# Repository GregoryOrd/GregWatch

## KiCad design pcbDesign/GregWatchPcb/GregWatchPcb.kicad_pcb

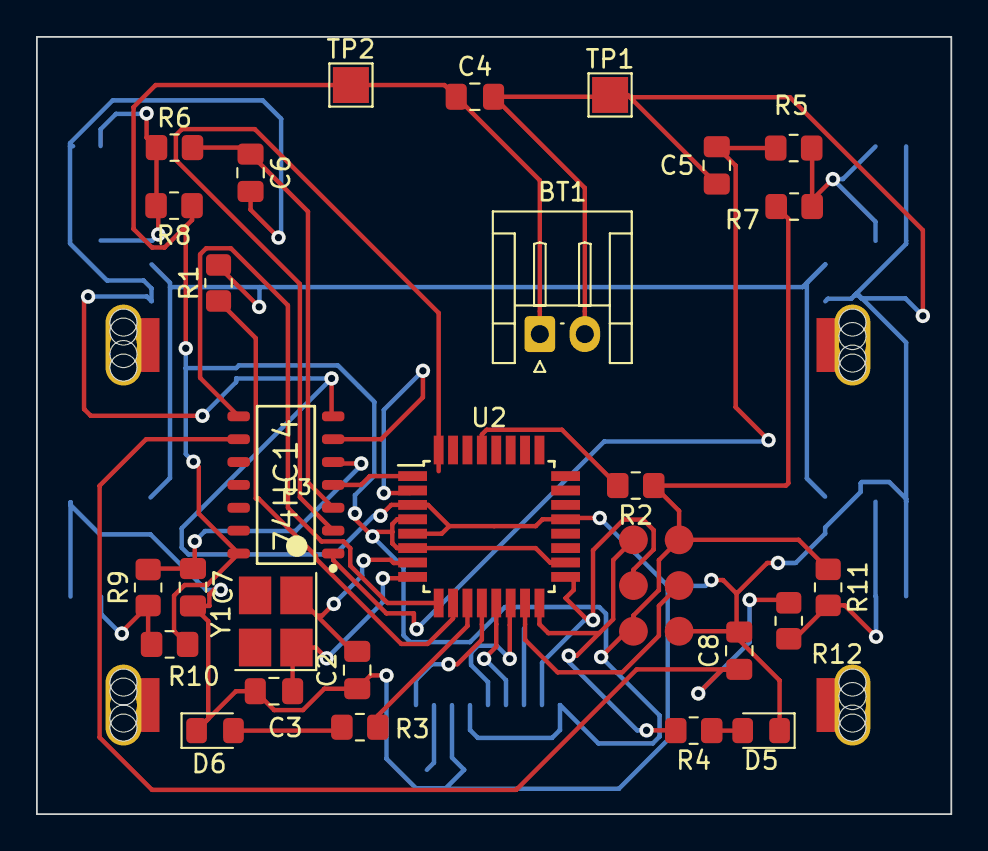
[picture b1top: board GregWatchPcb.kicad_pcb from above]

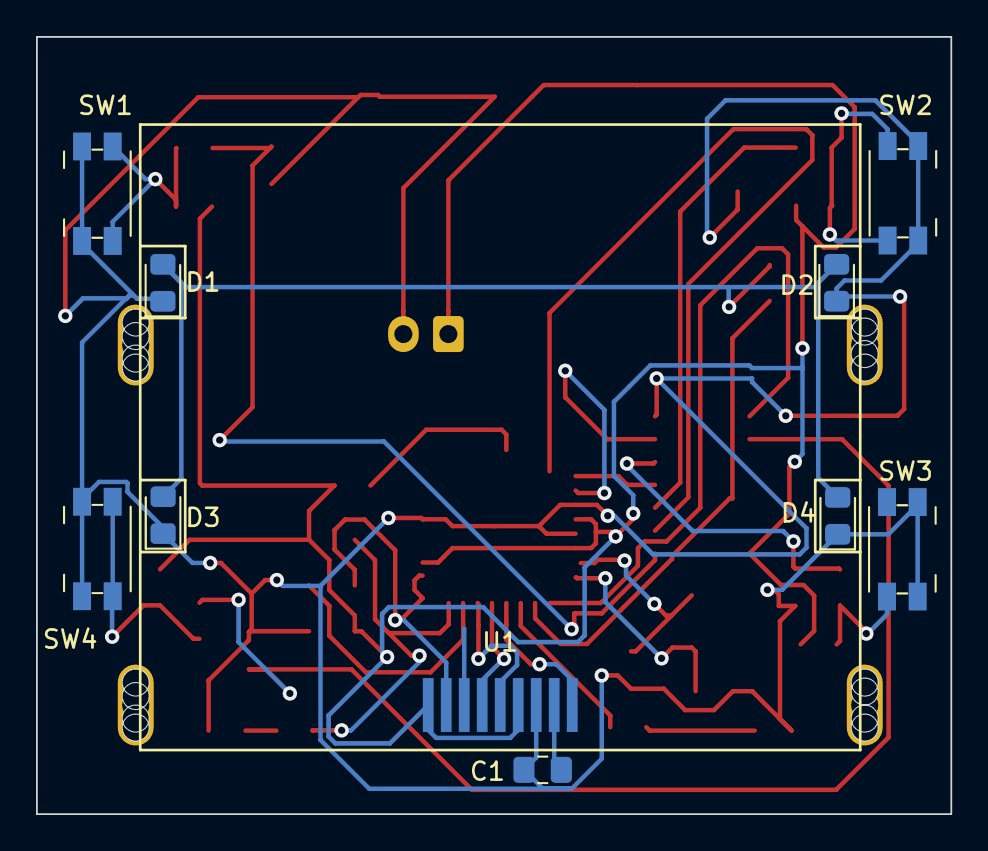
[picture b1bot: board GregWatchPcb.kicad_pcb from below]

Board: 2 copper layers, 50.8 x 43.2 mm, 38 parts (10 on the bottom side), 29 nets.

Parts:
BT1: Battery_Cell; JST_EH_S2B-EH_1x02_P2.50mm_Horizontal
C1, C5, C6, C7, C8: 0.1u; C_0805_2012Metric_Pad1.18x1.45mm_HandSolder
C2, C3: 22p; C_0805_2012Metric_Pad1.18x1.45mm_HandSolder
C4: 10u; C_0805_2012Metric_Pad1.18x1.45mm_HandSolder
D1, D2, D3, D4, D5, D6: LED; LED_0805_2012Metric_Pad1.15x1.40mm_HandSolder
J1: AVR-ISP-6
R1, R3, R4: 100; R_0805_2012Metric_Pad1.20x1.40mm_HandSolder
R2, R5, R6, R7, R8, R9, R10, R11, R12: 10k; R_0805_2012Metric_Pad1.20x1.40mm_HandSolder
SW1, SW2, SW3, SW4: SW_Push; Panasonic_EVQPUJ_EVQPUA
TP1, TP2: TestPoint; TestPoint_Pad_2.0x2.0mm
U1: Nokia_5110_LCD; Nokia_5110-3310_LCD-F.Paste-B.Paste
U2: ATmega328P-AU; TQFP-32_7x7mm_P0.8mm
U3: 74HC14; Texas_Instruments-CD74HC14-Level_C
Y1: 16M; Crystal_SMD_3225-4Pin_3.2x2.5mm_HandSoldering

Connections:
unnamed: BT1.1, C4.1, J1.2, J1.5, R2.1, R7.1, R8.1, R10.1, R11.1, TP2.1, U1.4, U1.9, U2.4, U2.6, U2.18, U3.14
unnamed: BT1.2, C1.1, C2.1, C3.1, C4.2, C5.2, C6.2, C7.2, C8.2, D1.1, D2.1, D3.1, D4.1, D5.1, D6.1, J1.6, SW1.1, SW2.1, SW3.1, SW4.1, TP1.1, U1.3, U2.3, U2.5, U2.21, U3.7
unnamed: C1.2, U1.2
unnamed: C2.2, U2.7, Y1.2
unnamed: C3.2, U2.8, Y1.1
unnamed: C5.1, R5.2, U3.1
unnamed: C6.1, R6.2, U3.3
unnamed: C7.1, R9.2, U3.5
unnamed: C8.1, R12.2, U3.9
unnamed: D1.2, D2.2, D3.2, D4.2, R1.2
unnamed: D5.2, R4.1
unnamed: D6.2, R3.1
unnamed: J1.1, R4.2, U2.16
unnamed: J1.3, U1.8, U2.17
unnamed: J1.4, U1.7, U2.15
unnamed: R1.1, U2.10
unnamed: R2.2, U2.29
unnamed: R3.2, U2.11
unnamed: R5.1, R7.2, SW1.2
unnamed: R6.1, R8.2, SW2.2
unnamed: R9.1, R10.2, SW3.2
unnamed: R11.2, R12.1, SW4.2
unnamed: U1.1, U2.12
unnamed: U1.5, U2.14
unnamed: U1.6, U2.13
unnamed: U2.1, U3.4
unnamed: U2.2, U3.6
unnamed: U2.9, U3.8
unnamed: U2.32, U3.2

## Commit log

2021-04-19 First code commit with copied code for an example to drive the LCD screen
2021-04-19 Actual first code commit.
2021-04-19 Correcting GregBuild config file and the load.sh and copy.sh scripts
2021-04-19 Now showing a timer at 00:00 and switching to 00:01 after one second
2021-04-20 Major cleanup. Now have the display bit patterns for numbers 0 through 2 as well as a colon. Can run through a clock like pattern with minutes and hours going up to 22.
2021-04-27 Added -fno-common linker flag
2021-04-27 Adding the bit pattern for number 3
2021-04-27 Adding reset display functions and using loops to run through minutes and hours.
2021-04-27 Add bit pattern for number 4 and made number 3 a touch wider.
2021-04-27 Shortened number of lines in run through functions.
2021-04-28 Add bit patterns for six and seven
2021-04-28 Added number 7
2021-04-28 Improved bit pattern for 7 to have a diagonal leg.
2021-04-28 Bit pattern for number 8
2021-04-28 Added bit pattern for 9
2021-04-28 Cleanup the runThroughMinutes and runThroughHours functions.
2021-04-29 Restructured the repo. Prep work for linking with a hardware sim library. Need to wait on some more functionality to be built into GregBuild to support this.
2021-04-29 First failing test after GregBuild update. hardwareSim.so and timeSim.so now found under the repo/s lib directory.
2021-04-29 Makefile for creating the hardware simulator libraries.
2021-04-29 Rename and passing the first test.
2021-04-29 Created TODOs.txt
2021-04-30 Test cases for all functions in spi.h. Some commented out while waiting for updates to GregTest
2021-04-30 Back out of the SPI directory
2021-05-01 Move around spi.h includes
2021-05-01 Added testNokia5110.c
2021-05-01 Major reorganization of the repo. Trying to think about the structure as features and subfeatures.
2021-05-01 Create timeDefs.h. Rename functions/variables to match that right now, our display is minutes:seconds not hours:minutes.
2021-05-01 Added TestTimeDefs.c
2021-05-02 Adding compiler option to allow for G_EXPECT_CALLs
2021-05-02 Using expect calls and bool comparisions now that they are supported by GregTest.
2021-05-04 Wrote test cases for testStopWatch.c
2021-05-04 Added test cases in testLetters16x12.c
2021-05-07 Switching to a timer interrupt instead of _delay_ms for the stop watch.
2021-05-07 Adding a stopWatchDone flag for hitting 60 minutes,
2021-05-08 Add #define IDR to the hardwareSim to get rid of error when compiling for tests.
2021-05-08 Move time related files to timer directory
2021-05-08 Pull presentation folder out a layer
2021-05-08 Removed the screenApi layer folder
2021-05-09 First version of the stop and start button.
2021-06-04 Created fuses.txt to record what configuration is being used for the fuse bits on the AtMega328p microcontroller.
2021-06-06 Using INT0 for the pause button.
2021-06-10 Starting to put together a schematic using KiCad
2021-06-11 Move SPI lines for screen to the right
2021-06-11 Using nokia 5110 schematic symbol
2021-06-11 Add backlight LEDs and button circuits
2021-06-11 Added resistance and capacitance values to all resistors and capacitors
2021-06-11 Annotated schematic and corrected some RC values
2021-06-11 Added note about part names/numbers for purchasing components
2021-06-13 Added footprints to the schematic components
2021-06-13 Add number of each component nessecary to components list text file
2021-06-13 Exported schematic as netlist and imported it into Pcbnew
2021-06-15 Screen and backlight LED components arranged on the back of the PCB
2021-06-15 Move LEDs and flip capacitor and resistor to make sure things fit under the clip on screen
2021-06-15 Moved switched and ISP pad in place. Only partial connections so far.
2021-06-16 Switch interrupt to rising edge for on-press behaviour instead of on-release behaviour
2021-06-16 First button connected
2021-06-16 Top two buttons connected
2021-06-16 Connected the ICSP programmer pad
2021-06-17 Connected the third button
2021-06-17 Place and routed the power and IC components
2021-06-17 Placed all components. No traces yet.
2021-06-17 Added connection for all components on the board
2021-06-20 Add battery to schematic and JST connector for the battery to the PCB
2021-06-20 Moved some of the component labels
2021-06-24 Update copy.sh and sim makefile
2021-08-01 Update fuses.txt to specify fuses for internal vs external oscillator
2021-08-02 Change F_CPU now that we are using the 8MHz internal oscillator
2021-12-11 Added backlight control on PORTD4
2021-12-12 Now using light sensor to toggle backlight
2021-12-12 Add wiring note to lightSensor.h until PCB schematics can be updated
2021-12-12 Change buttons to use pin change rather than external interrupts.
    The light sensor temporarily disabled during this change.
    Using pin change rather than external interrupts so that we can
    have four buttons; there are only two external interrupts.
    Will change the light sensor to a different pin so that we can have all
    of the buttons come into pins beside each other.
2021-12-12 Use for loop instead of nested ifs to search through the buttons
2021-12-12 Change backlight pin and re-enable the lightsensor.
2021-12-12 Create deviceDrivers folder
2021-12-12 Move global interrupt enabling to main init function instead of timer init
2021-12-12 Added some TODOs
2021-12-12 Change to timer1 to reduce clock drift.
    Also move timeState and timeDefs into timer.
2021-12-12 Added a TODO
2022-09-28 Using host name for raspberry pi
